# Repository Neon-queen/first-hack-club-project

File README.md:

# Starbie 2-Key Project

This is my first Hack Club hardware project made with KiCad.  
It’s a star-shaped PCB with two push buttons and connectors.  
The board is designed for simple input control and learning PCB design.

## Features
- Star-shaped PCB design
- Two push buttons
- Connector pins for external components

## Tools Used
- KiCad for PCB design
- Hack Club Half Life for project guidance

## Images
## Project Images

## Bill of Materials
See [bom.csv](bom.csv) for the list of components.

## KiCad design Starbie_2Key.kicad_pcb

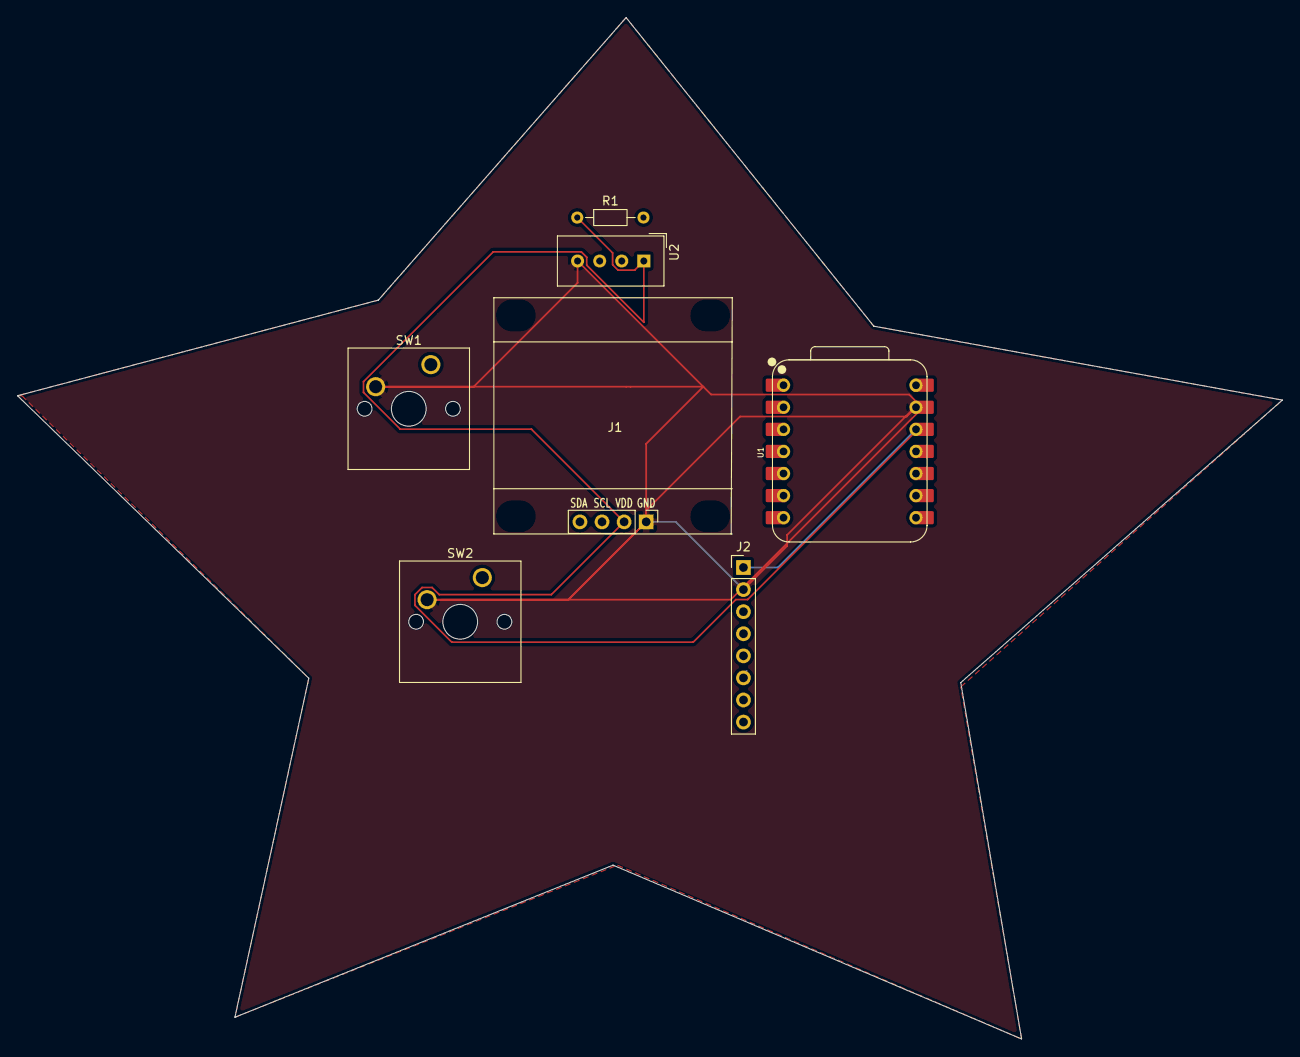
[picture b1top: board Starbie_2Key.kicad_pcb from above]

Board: 2 copper layers, 145.5 x 117.5 mm, 7 parts (0 on the bottom side), 2 nets.

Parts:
J1: Conn_01x04_Pin; Display_128x64_096_I2C
J2: Conn_01x08_Pin; PinHeader_1x08_P2.54mm_Vertical
R1: 10K; R_Axial_DIN0204_L3.6mm_D1.6mm_P7.62mm_Horizontal
SW1, SW2: SW_Push; SW_Cherry_MX_1.00u_PCB
U1: XIAO-ESP32-C3-SMD; XIAO-ESP32-C6-DIP
U2: DHT11; Aosong_DHT11_5.5x12.0_P2.54mm

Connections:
+3.3V: J1.2, J2.1, R1.1, U1.12 (3V3_OUT), U2.1 (VDD)
GND: J1.1, J2.2, SW1.2 (2_2), SW2.2 (2_2), U1.13 (GND), U2.4 (GND)
